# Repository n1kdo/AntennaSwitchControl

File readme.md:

# N1KDO IOT Antenna Switch Control

This project is intended to operate a remote antenna switch.  

It supports (up to) a 2-radio, 8-antenna switch.  2x6 switches for fine.  Active-hi
or active low compatible.

Why IOT?  That's really about WiFi.  The board uses WiFi to connect to your network,
which means that only the power leads need to be protected from Zeus, not 14 +/- wires.  

I have built matching "band-decoders" to interface with my Elecraft HF radios.  
The band decoders detect a band change on the radio and send a API request to 
the switch control board to request an antenna for that band.  If no antenna 
is available, the band decoder will activate the K3s' "TX INHIBIT" lead and 
prevent the radio from transmitting into the wrong antenna or no antenna.

The Band Selector (radio interface) is [here](https://github.com/n1kdo/BandSelector) &mdash;
This is the other component for this project, you will need _two_ &mdash;  one for each radio.

See the Ecosystem diagram, below.

## Ecosystem

## Bill of Materials

* [Bill of Materials](BOM.md)
* The approximate cost to buy these parts is about $106.

## Board Image

# UI Images

## "Control Panel" Image

## Antenna Setup UI

## Radio Setup UI

## Network Setup UI

n1kdo 20251124

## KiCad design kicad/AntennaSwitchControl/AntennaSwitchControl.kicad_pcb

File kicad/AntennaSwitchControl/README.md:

# Antenna Switch Control (Hardware)

This is a board that allows a Raspberry Pi Pico-W to control 16 SPST relays.

The original purpose is to provide better automation for a 2-in, 6-out remote antenna switch, but
it is built with extra capacity to allow a 2-in, 8-out remote switch as well.

## 3D image from KiCad

## Real World Image

20250324 n1kdo

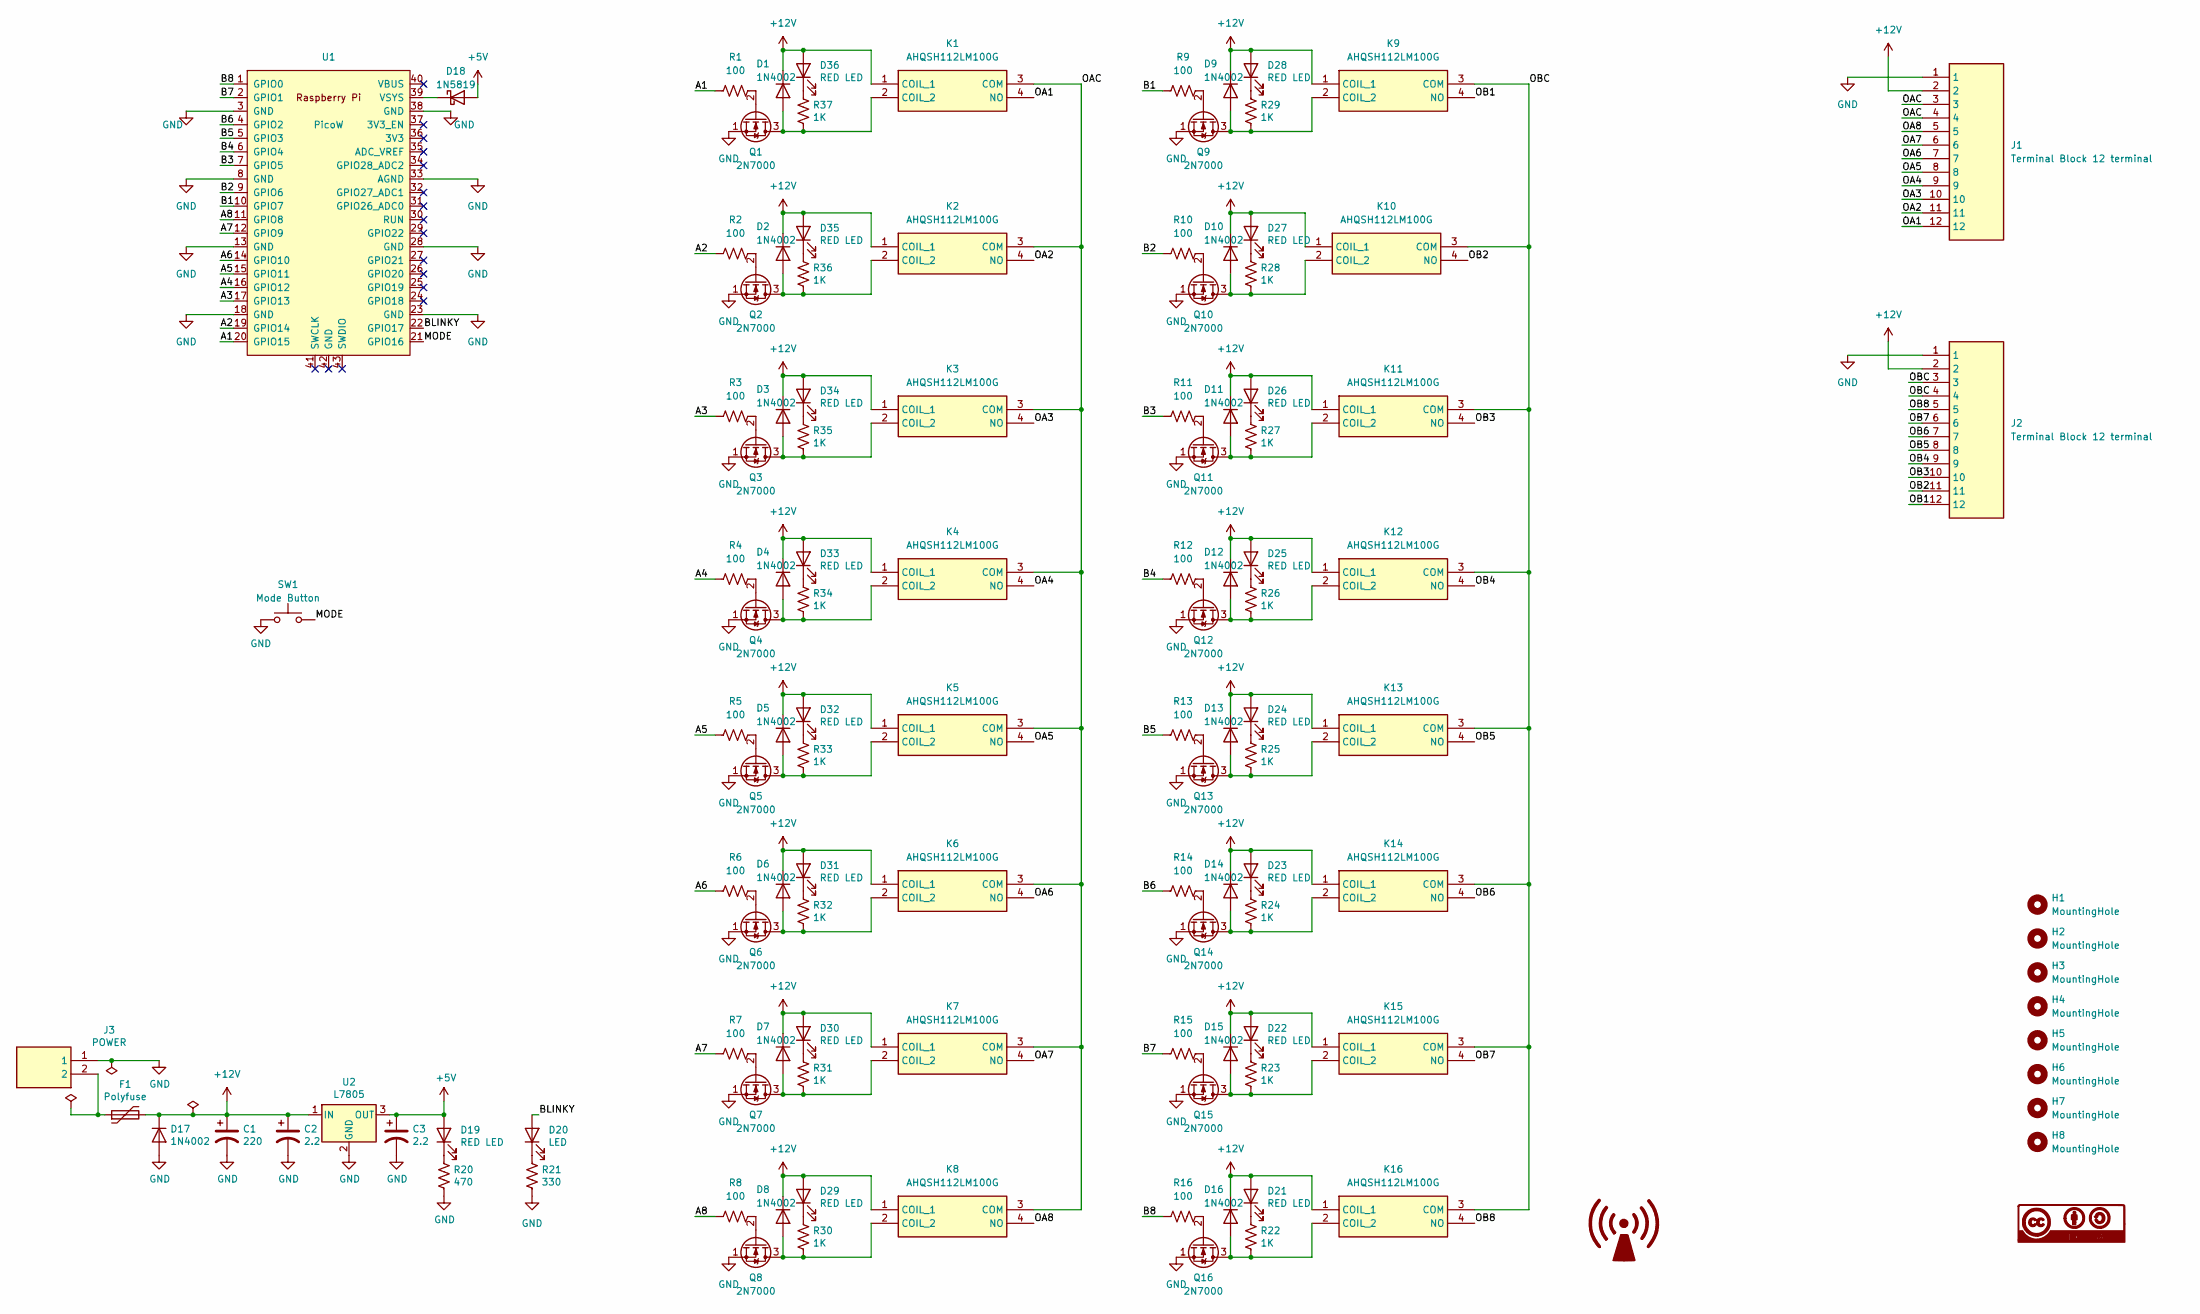
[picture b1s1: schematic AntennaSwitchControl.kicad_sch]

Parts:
C1: 220; CP_Radial_D8.0mm_P3.50mm; Part ECA-1EM221
C2, C3: 2.2; CP_Radial_D5.0mm_P2.50mm; Part EEU-FC1H2R2H
D1, D2, D3, D4, D5, D6, D7, D8, D9, D10, D11, D12, D13, D14, D15, D16: 1N4002; D_DO-41_SOD81_P7.62mm_Horizontal
D17: 1N4002; D_DO-15_P10.16mm_Horizontal; Part 1n4002
D18: 1N5819; D_DO-41_SOD81_P10.16mm_Horizontal
D19: RED LED; LED_D3.0mm
D20: LED; LED_D3.0mm
D21, D22, D23, D24, D25, D26, D27, D28, D29, D30, D31, D32, D33, D34, D35, D36: RED LED; LED_D3.0mm; Part AP2012HD
F1: Polyfuse; RUEF090; Part 30R090UU
H1, H2, H3, H4, H5, H6, H7, H8: MountingHole; MountingHole_3.5mm_Pad
J1, J2: Terminal Block 12 terminal; CUI_TBP04R1-500-12BE; Mouser Part Number 179-TBP04R1-500-12BE
J3: POWER; CUI_TBP04R1-500-02BE; Part TBP04R1-500-02BE; Mouser Part Number 179-TBP04R1-500-02BE
K1, K2, K3, K4, K5, K6, K7, K8, K9, K10, K11, K12, K13, K14, K15, K16: AHQSH112LM100G; AHQSH112LM112G; Mouser Part Number 523-AHQSH105LM100G
Q1, Q2, Q3, Q4, Q5, Q6, Q7, Q8, Q9, Q10, Q11, Q12, Q13, Q14, Q15, Q16: 2N7000; TO-92_Inline
R1, R2, R3, R4, R5, R6, R7, R8, R9, R10, R11, R12, R13, R14, R15, R16: 100; R_Axial_DIN0207_L6.3mm_D2.5mm_P7.62mm_Horizontal
R20: 470; R_Axial_DIN0207_L6.3mm_D2.5mm_P7.62mm_Horizontal; Part ERJ-6GEYJ471V
R21: 330; R_Axial_DIN0207_L6.3mm_D2.5mm_P7.62mm_Horizontal; Part ERJ-6GEYJ471V
R22, R23, R24, R25, R26, R27, R28, R29, R30, R31, R32, R33, R34, R35, R36, R37: 1K; R_Axial_DIN0207_L6.3mm_D2.5mm_P7.62mm_Horizontal; Part ERJ-6GEYJ471V
SW1: Mode Button; GB215AHB; part GB215AH
U1: PicoW; RPi_PicoW_SMD_TH
U2: L7805; TO-220-3_Vertical; Part L7805CDT-TR

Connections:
+5V: C3.1, D18.2 (A), D19.2 (A), U2.3 (OUT)
+12V: C1.1, C2.1, D1.1 (K), D2.1 (K), D3.1 (K), D4.1 (K), D5.1 (K), D6.1 (K), D7.1 (K), D8.1 (K), D9.1 (K), D10.1 (K), D11.1 (K), D12.1 (K), D13.1 (K), D14.1 (K), D15.1 (K), D16.1 (K), D17.1 (K), D21.2 (A), D22.2 (A), D23.2 (A), D24.2 (A), D25.2 (A), D26.2 (A), D27.2 (A), D28.2 (A), D29.2 (A), D30.2 (A), D31.2 (A), D32.2 (A), D33.2 (A), D34.2 (A), D35.2 (A), D36.2 (A), F1.2, J1.2, J2.2, K1.1 (COIL_1), K2.1 (COIL_1), K3.1 (COIL_1), K4.1 (COIL_1), K5.1 (COIL_1), K6.1 (COIL_1), K7.1 (COIL_1), K8.1 (COIL_1), K9.1 (COIL_1), K10.1 (COIL_1), K11.1 (COIL_1), K12.1 (COIL_1), K13.1 (COIL_1), K14.1 (COIL_1), K15.1 (COIL_1), K16.1 (COIL_1), U2.1 (IN)
/A1: R1.1, U1.20 (GPIO15)
/A2: R2.1, U1.19 (GPIO14)
/A3: R3.1, U1.17 (GPIO13)
/A4: R4.1, U1.16 (GPIO12)
/A5: R5.1, U1.15 (GPIO11)
/A6: R6.1, U1.14 (GPIO10)
/A7: R7.1, U1.12 (GPIO9)
/A8: R8.1, U1.11 (GPIO8)
/B1: R9.1, U1.10 (GPIO7)
/B2: R10.1, U1.9 (GPIO6)
/B3: R11.1, U1.7 (GPIO5)
/B4: R12.1, U1.6 (GPIO4)
/B5: R13.1, U1.5 (GPIO3)
/B6: R14.1, U1.4 (GPIO2)
/B7: R15.1, U1.2 (GPIO1)
/B8: R16.1, U1.1 (GPIO0)
/BLINKY: D20.2 (A), U1.22 (GPIO17)
/MODE: SW1.2, U1.21 (GPIO16)
/OA1: J1.12, K1.4 (NO)
/OA2: J1.11, K2.4 (NO)
/OA3: J1.10, K3.4 (NO)
/OA4: J1.9, K4.4 (NO)
/OA5: J1.8, K5.4 (NO)
/OA6: J1.7, K6.4 (NO)
/OA7: J1.6, K7.4 (NO)
/OA8: J1.5, K8.4 (NO)
/OAC: J1.3, J1.4, K1.3 (COM), K2.3 (COM), K3.3 (COM), K4.3 (COM), K5.3 (COM), K6.3 (COM), K7.3 (COM), K8.3 (COM)
/OB1: J2.12, K9.4 (NO)
/OB2: J2.11, K10.4 (NO)
/OB3: J2.10, K11.4 (NO)
/OB4: J2.9, K12.4 (NO)
/OB5: J2.8, K13.4 (NO)
/OB6: J2.7, K14.4 (NO)
/OB7: J2.6, K15.4 (NO)
/OB8: J2.5, K16.4 (NO)
/OBC: J2.3, J2.4, K9.3 (COM), K10.3 (COM), K11.3 (COM), K12.3 (COM), K13.3 (COM), K14.3 (COM), K15.3 (COM), K16.3 (COM)
GND: C1.2, C2.2, C3.2, D17.2 (A), J1.1, J2.1, J3.1, Q1.1 (S), Q2.1 (S), Q3.1 (S), Q4.1 (S), Q5.1 (S), Q6.1 (S), Q7.1 (S), Q8.1 (S), Q9.1 (S), Q10.1 (S), Q11.1 (S), Q12.1 (S), Q13.1 (S), Q14.1 (S), Q15.1 (S), Q16.1 (S), R20.2, R21.2, SW1.1, U1.3 (GND), U1.8 (GND), U1.13 (GND), U1.18 (GND), U1.23 (GND), U1.28 (GND), U1.33 (AGND), U1.38 (GND), U2.2 (GND)
unnamed: D1.2 (A), K1.2 (COIL_2), Q1.3 (D), R37.2
unnamed: D2.2 (A), K2.2 (COIL_2), Q2.3 (D), R36.2
unnamed: D3.2 (A), K3.2 (COIL_2), Q3.3 (D), R35.2
unnamed: D4.2 (A), K4.2 (COIL_2), Q4.3 (D), R34.2
unnamed: D5.2 (A), K5.2 (COIL_2), Q5.3 (D), R33.2
unnamed: D6.2 (A), K6.2 (COIL_2), Q6.3 (D), R32.2
unnamed: D7.2 (A), K7.2 (COIL_2), Q7.3 (D), R31.2
unnamed: D8.2 (A), K8.2 (COIL_2), Q8.3 (D), R30.2
unnamed: D9.2 (A), K9.2 (COIL_2), Q9.3 (D), R29.2
unnamed: D10.2 (A), K10.2 (COIL_2), Q10.3 (D), R28.2
unnamed: D11.2 (A), K11.2 (COIL_2), Q11.3 (D), R27.2
unnamed: D12.2 (A), K12.2 (COIL_2), Q12.3 (D), R26.2
unnamed: D13.2 (A), K13.2 (COIL_2), Q13.3 (D), R25.2
unnamed: D14.2 (A), K14.2 (COIL_2), Q14.3 (D), R24.2
unnamed: D15.2 (A), K15.2 (COIL_2), Q15.3 (D), R23.2
unnamed: D16.2 (A), K16.2 (COIL_2), Q16.3 (D), R22.2
unnamed: D18.1 (K), U1.39 (VSYS)
unnamed: D19.1 (K), R20.1
unnamed: D20.1 (K), R21.1
unnamed: D21.1 (K), R22.1
unnamed: D22.1 (K), R23.1
unnamed: D23.1 (K), R24.1
unnamed: D24.1 (K), R25.1
unnamed: D25.1 (K), R26.1
unnamed: D26.1 (K), R27.1
unnamed: D27.1 (K), R28.1
unnamed: D28.1 (K), R29.1
unnamed: D29.1 (K), R30.1
unnamed: D30.1 (K), R31.1
unnamed: D31.1 (K), R32.1
unnamed: D32.1 (K), R33.1
unnamed: D33.1 (K), R34.1
unnamed: D34.1 (K), R35.1
unnamed: D35.1 (K), R36.1
unnamed: D36.1 (K), R37.1
unnamed: F1.1, J3.2
unnamed: Q1.2 (G), R1.2
unnamed: Q2.2 (G), R2.2
unnamed: Q3.2 (G), R3.2
unnamed: Q4.2 (G), R4.2
unnamed: Q5.2 (G), R5.2
unnamed: Q6.2 (G), R6.2
unnamed: Q7.2 (G), R7.2
unnamed: Q8.2 (G), R8.2
unnamed: Q9.2 (G), R9.2
unnamed: Q10.2 (G), R10.2
unnamed: Q11.2 (G), R11.2
unnamed: Q12.2 (G), R12.2
unnamed: Q13.2 (G), R13.2
unnamed: Q14.2 (G), R14.2
unnamed: Q15.2 (G), R15.2
unnamed: Q16.2 (G), R16.2

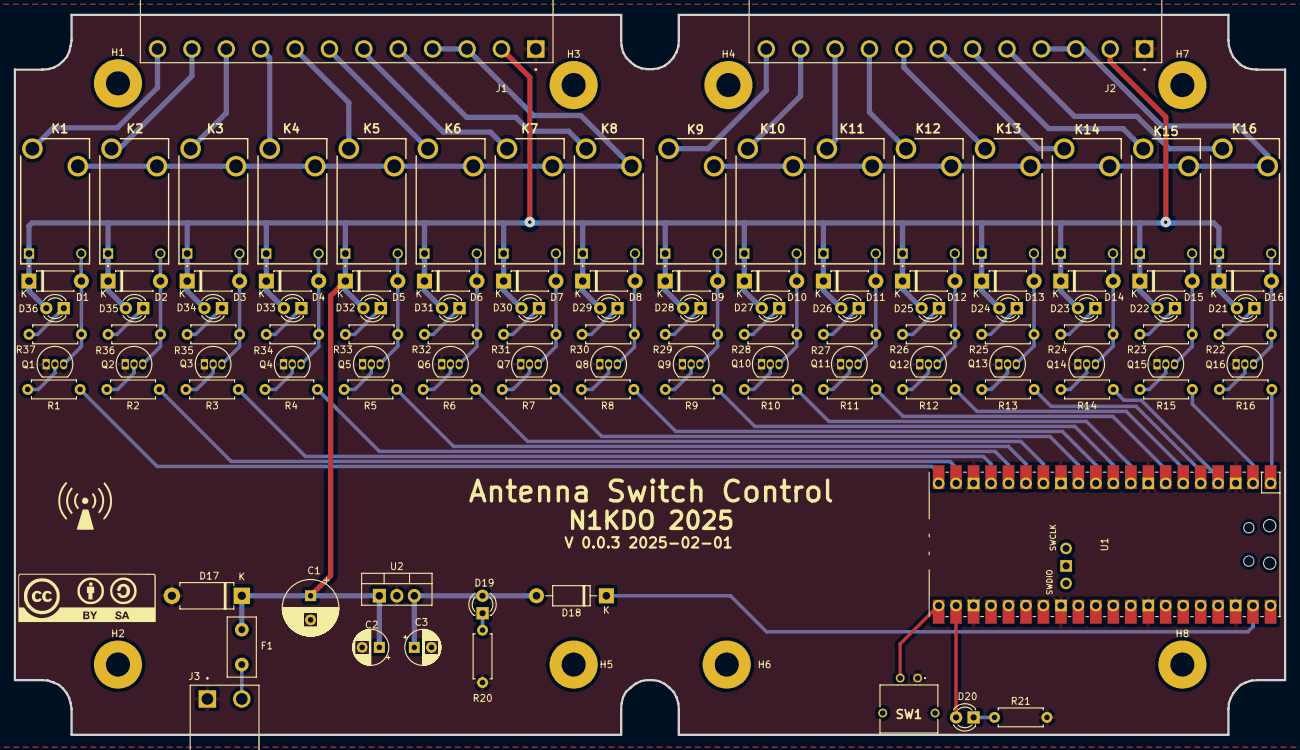
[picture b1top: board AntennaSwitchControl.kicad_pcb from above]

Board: 2 copper layers, 184.7 x 104.7 mm, 122 parts (0 on the bottom side), 91 nets.

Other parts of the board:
G1: LOGO; non-ionizing-bigger
Ref**: Val**; CC-BY-SA

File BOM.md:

# Bill of Materials for Antenna Switch Controller

This is the Bill of Materials for the N1KDO Antenna Switch Controller.

All the parts -- except the circuit boards -- were ordered from Mouser.com.

The circuit boards came from Oshpark.com.

## Antenna Switch Controller Board Bill of Materials

| ID                                                                           | Description                                                             | Manufacturer          | Part Number      | Qty | Price |   Extended |
|------------------------------------------------------------------------------|-------------------------------------------------------------------------|-----------------------|------------------|----:|------:|-----------:|
| C1                                                                           | Aluminum Electrolytic Capacitors - Radial Leaded 220uF 25V              | Panasonic             | ECA-1EM221       |   1 |  0.28 |       0.28 |
| C2,C3                                                                        | Aluminum Electrolytic Capacitors - Radial Leaded 2.2uF 50volts AEC-Q200 | Panasonic             | EEU-FC1H2R2H     |   2 |  0.12 |       0.24 |
| D1,D2,D3,D4,D5,D6,D7,D8,D9,D10,<br/>D11,D12,D13,D14,D15,D16,D17              | Rectifiers Diode - DO-41 - 100V - 1A                                    | Diotec                | 1N4002           |  17 |  0.06 |       1.02 |
| D18                                                                          | Schottky Diodes & Rectifiers Vr/40V Io/1A                               | STMicroelectronics    | 1N5819           |   1 |  0.21 |       0.21 |
| D19,D20,D21,D22,D23,D24,D25,D26,D27,<br/>D28,D29,D30,D31,D32,D33,D34,D35,D36 | Standard LEDs - Through Hole Red Diffused                               | Lite-On               | LTL-4221N        |  18 |  0.19 |       3.42 |
| F1                                                                           | Resettable Fuses - PPTC .9A 30V 100A Imax                               | LittelFuse            | RUEF090          |   1 |  0.61 |       0.61 |
| J1,J2                                                                        | Headers & Wire Housings 2.54MM SR RA 12P HDR AU L-PRO SHRD              | Molex                 | 70553-0116       |   2 |  2.10 |       4.20 | 
| J3                                                                           | Headers & Wire Housings R/A HDR 2P low profile single                   | Molex                 | 70553-0001       |   1 |  0.86 |       0.86 |
| K1,K2,K3,K4,K5,K6,K7,K8,<br/>K9,K10,K11,K12,K13,K14,K15,K16                  | General Purpose Relays Commercial Relay Rated Carrying Current 10A      | Amphenol Anytek       | AHQSH112LM100G   |  16 |  0.53 |       8.48 |
| Q1,Q2,Q3,Q4,Q5,Q6,Q7,Q8,<br/>Q9,Q10,Q11,Q12,Q13,Q14,Q15,Q16                  | MOSFET 60V 200mA 5 Ohm Single N-Channel TO-92                           | onsemi / Fairchild    | 2N7000           |  16 |  0.38 |       6.08 |
| R1,R2,R3,R4,R5,R6,R7,R8<br/>R9,R10,R11,R12,R13,R14,R15,R16                   | Carbon Film Resistors - Through Hole 1/4W 100 Ohm 5%                    | Yageo                 | CFR-25JB-52-100R |  15 |  0.04 |       0.60 |
| R20                                                                          | Carbon Film Resistors - Through Hole 1/4W 470 Ohm 5%                    | Yageo                 | CFR-25JB-52-470R |   1 |  0.02 |       0.02 |
| R21                                                                          | Carbon Film Resistors - Through Hole 1/4W 330 Ohm 5%                    | Yageo                 | CFR-25JB-52-330R |   1 |  0.02 |       0.02 |
| R22,R23,R24,R25,R26,R27,R28,R29,<br/>R30,R31,R32,R33,R34,R35,R36,R37         | Carbon Film Resistors - Through Hole 1 kOhms 250 mW 5 %                 | Yageo                 | CFR-25JB-1K0     |  16 |  0.02 |       0.32 |
| SW1                                                                          | Pushbutton Switches SPST OFF(ON) R/A WHT                                | NKK Switches          | GB215AH-B        |   1 |  4.35 |       4.35 |
| SW1 (cap)                                                                    | Switch Bezels / Switch Caps .157" RND BLK CAP                           | NKK Switches          | AT4063A          |   1 |  0.52 |       0.52 |
| U1                                                                           | Single Board Computers Raspberry Pi Pico W                              | Raspberry Pi          | SC0918           |   1 |  6.00 |       6.00 |
| U3                                                                           | Linear Voltage Regulators 5.0V 1.5A Positive                            | STMicroelectronics    | L7805CV          |   1 |  0.48 |       0.48 |
| Enclosure                                                                    | Enclosures, Boxes, & Cases FR ABS w/Flanged Lid 7.6x4.4x2.2" Black      | Hammond Manufacturing | 1591XXEFLBK      |   1 | 12.84 |      12.84 |
| P1, P2                                                                       | Headers & Wire Housings HSG 12P SINGLE ROW POSITIVE LATCH               | Molex                 | 50-57-9412       |   2 |  0.45 |       0.90 |
| P3                                                                           | Headers & Wire Housings HSG 2P SINGLE ROW POSITIVE LATCH                | Molex                 | 50-57-9402       |   1 |  0.26 |       0.26 |
| Pins                                                                         | Headers & Wire Housings TERMINAL 22-24 BULK                             | Molex                 | 16-02-1125       |  26 |  0.15 |       3.90 |
| PCB                                                                          | N1KDO Antenna Switch Control PCB Band Selector Board PCB V 0.0.2        | Oshpark               |                  |   1 | 50.08 |      50.08 |
| **Total**                                                                    |                                                                         |                       |                  |     |       | **105.69** |

Approximate Total Project Cost $106.

n1kdo 20250105

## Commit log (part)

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2024-07-14 add gitignore
2024-07-14 add requirements.txt
2024-07-21 running on real hardware now.
2024-07-27 building API endpoints
2024-08-03 rename
2024-08-03 some configuration working now.
2024-08-04 UI is functioning.
2024-08-04 add some docs
2024-08-18 selected antennas was not properly non-volatile
2024-09-07 wifi network resiliency & ui cleanup
    pulled in latest picow_network.py and
    and morse_code.py from kpa500 project
    made ui bottom line links more consistent.
2024-09-07 styles cleanup
2024-09-28 add antenna_bands array to status message.
2024-09-29 band change response changed to include the change
2024-09-29 band change faiiure response message changed
    updated to latest morse code and pico network
2024-09-29 allow 20 chars for antenna names
2024-10-30 update readme files
2024-10-30 move images
2024-10-30 fix glaring errors
2024-10-30 add BOM, clean up schematic
2024-10-30 update licensd docs
2024-10-30 update license docs
2024-10-31 added molex pins for connectors
2024-10-31 udpate readme
2024-11-16 allow configuring hostname
2024-11-17 actually use buffer previously allocated.
    this reduces heap fragmentation.
2024-11-17 smallerify favicon
2024-11-17 loader improvements
    --force does not try to delete non-empty dirs
    read manifest file instead of hard-coded manifest data
2024-12-14 add support for NO antenna selected
    tolerate some connection failures better
    use constants for http response codes
2024-12-31 logging now supports should_log
    plus tiny micropython optimization
2024-12-31 slight performance work
2024-12-31 more performance work
2024-12-31 add experimental six-panes.html
2024-12-31 latest picow_network.py
2024-12-31 uggh. fix ssid bug
2024-12-31 fix default config item names
2025-01-04 move json encoding to http_server
2025-01-05 add pricing to BOM
2025-01-11 very minor optimizations
2025-01-11 set rtc so log data is more useful
2025-01-12 another update to loader.py
2025-01-12 don't try to create directories that exist already.
2025-01-19 add watchdog
2025-01-26 adjust logging
    fix up network connection messages
2025-02-01 v 2.0 hardware.
    swap out connectors
    move connectors to back of board
    reallocate port outputs
    move pico-w to edge of board.
2025-02-25 misc fixes
2025-03-13 api change
2025-03-13 fix off by one error.
2025-03-15 add radio_number to status result when one radio specified.
2025-03-16 add new board image
2025-03-16 status API changes
2025-03-18 fix off-by-one.
    still ugly
2025-03-20 make more async.
    drain output more.
2025-03-20 disable watchdog for now
2025-03-20 make constants more constant
2025-03-24 more logging for weird scenarios
2025-03-24 # Conflicts: # src/switch_control/http_server.py
2025-03-24 doc updates
2025-03-24 more doc updates
2025-03-24 even more doc updates
2025-04-24 re-enable the letter O
2025-04-24 update http_server
    this updated version should use less heap
2025-04-24 make loader tolerate keyboardinterrupt better
2025-04-24 update to latest pyboard
2025-04-24 validate network is working by pinging gateway
2025-04-24 python version update
2025-04-25 allow status page reload time to be set from search parameter
2025-04-25 add update parameter to the 6 pages loaded by default.
2025-04-25 fix substr -> substring
2025-05-01 try to fix reconnect logic better
2025-05-01 optimizations
2025-05-02 clean up imports, improve logging
2025-05-02 make default password longer
2025-05-02 fix up debug logging
2025-05-03 fix logging
2025-05-03 log configuration post api failures
2025-07-25 make auto-update more reliable
2025-08-04 log level INFO please
2025-08-04 ui update recovery
2025-09-19 sent udp broadcasts of switch status
2025-10-16 Add ecosystem diagram
2025-10-26 pico_network v. 0.9.97 2025-10-26
    tries to make http query to router to verify
    network is up.
    clean up imports
    remove ping
2025-10-28 remove idea files
2025-10-28 remove idea dir
2025-10-28 update .gitignore again
    put idea files back
2025-11-05 update to latest http_server.py
    clean up some IDE warnings...
2025-11-06 use HTTP_STATUS_MOVED_PERMANENTLY constant
2025-11-24 new diagram
2025-12-15 image optimization
2025-12-15 latest loader.py
2025-12-15 update loader.py, enable watchdog
2025-12-22 don't try to set time when running as an AP.
2025-12-22 web pages refactoring
    code review by ChatGPT -- better results than I expected.
2025-12-22 ooof. did not mean to leave debug enabled.
2025-12-22 fix bug on dhcp toggle
2025-12-22 hardening; code cleanups
2025-12-27 update six-panes layout for more attracive arrangement
2025-12-27 update for latest picow_network
2025-12-28 turd polish 6-panes layout
2025-12-29 update some common code.
2025-12-29 fix edge case, improve logging
2025-12-29 don't allow empty config
2025-12-31 update .idea files
2025-12-31 cybersecurity
2025-12-31 SSID scan verbosity
2025-12-31 UDP broadcast, packing correctness
2025-12-31 add lock to select_antenna
2025-12-31 dictionary
2025-12-31 meeting with reality
2025-12-31 quieter logging while waiting for network
2025-12-31 add new --bootloader option
    this is for when you cannot access the
    little white button, perhaps because the
    module is in an enclosure
2026-01-01 latest pyboard.py from
2026-01-01 use cached_config_data.py to reduce flash write wear
2026-01-01 cleanup clutter
2026-01-01 use cached_config_data for config data
2026-01-01 grrr. turn off debug.
2026-01-07 try to improve layout on mobile devices
2026-01-07 improve layout on mobile devices
2026-01-07 better error messages on broadcast problems
2026-01-07 remove radio hostnames -- not being used.
2026-05-05 refactoring
2026-05-20 latest ntp.py has better error logging
2026-05-20 fix broadcast to use current config values. improve logging to enable debugging
2026-06-07 update to latest common code
2026-06-07 fix locking
2026-06-08 robustness in cpython test environment
2026-06-11 fix error payload typo.

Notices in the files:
kicad/AntennaSwitchControl/AntennaSwitchControl.kicad_pcb:
N1KDO 2024, 2025 CC-By-SA
